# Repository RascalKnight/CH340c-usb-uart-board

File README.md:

# USB-C to UART Converter Board

A 2-layer PCB that bridges USB-C to a TTL UART interface, built from 
scratch in KiCad using the CH340C USB-to-serial chip. Designed as a 
self-directed learning project to understand USB-C connector requirements, 
UART fundamentals, and full-cycle PCB design (schematic, layout, routing, 
and DRC resolution).

## Overview

This board allows a computer to communicate with a microcontroller or 
other UART-based device over USB-C, exposing TX, RX, GND, and VCC on a 
simple header. It replaces the need for a legacy USB-A to serial adapter 
with a compact, modern USB-C native solution.

## Key Design Features

- **CH340C** USB-to-UART bridge IC (crystal-less variant, integrated 
  clock)
- **USB-C receptacle (16P)** with correctly implemented CC1/CC2 pull-down 
  resistors (5.1kΩ) for proper USB-C power negotiation as a UFP (device)
- Standard **VBUS decoupling** (10µF + 0.1µF) and **V3 pin decoupling** 
  per CH340C's 5V power configuration
- Direct D+/D- routing from the USB-C connector to the CH340C's UD+/UD- 
  pins, verified pin-by-pin against the datasheet to avoid a reversed 
  connection
- 4-pin 2.54mm header output (VCC, GND, TXD, RXD) for standard jumper 
  wire compatibility

## Design Challenges Solved

- Diagnosed a **thermal relief spoke count DRC error** on the MCU's 
  fine-pitch GND pads, resolved by switching to a solid zone connection 
  for those specific pads
- Identified and resolved a **hole clearance violation** between the 
  USB-C connector's mechanical mounting holes and adjacent GND pads, 
  distinguishing it from a standard copper clearance issue
- Corrected a **decoupling capacitor placement issue** during layout 
  review, moving caps to sit directly against their associated IC pins
- Fixed an incorrect **RESET pull-up voltage rail** (was tied to 5V on a 
  3.3V-powered MCU) during an earlier related board, applying that lesson 
  here for correct voltage domain separation

## Files

- `.kicad_sch` / `.kicad_pcb` — full KiCad source project
- Schematic PDF export
- 3D board render

## Tools

Designed entirely in KiCad 10.

## Status

Schematic and layout complete, DRC clean. Not yet fabricated/assembled.

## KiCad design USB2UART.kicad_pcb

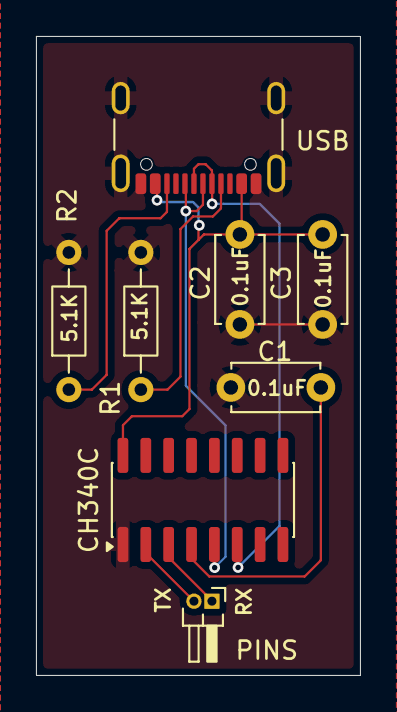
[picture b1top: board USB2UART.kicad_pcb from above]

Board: 2 copper layers, 18.0 x 35.5 mm, 8 parts (0 on the bottom side), 9 nets.

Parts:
C1, C2: 0.1uF; C_Disc_D4.7mm_W2.5mm_P5.00mm
C3: 10uF; C_Disc_D4.7mm_W2.5mm_P5.00mm
CH340C: CH340C; SOIC-16_3.9x9.9mm_P1.27mm
PINS: Conn_01x02_Pin; PinHeader_1x02_P1.00mm_Horizontal
R1, R2: 5.1K; R_Axial_DIN0204_L3.6mm_D1.6mm_P7.62mm_Horizontal
USB: USB_C_Receptacle_USB2.0_16P; USB_C_Receptacle_GCT_USB4105-xx-A_16P_TopMnt_Horizontal

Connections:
GND: C1.1, C2.1, C3.1, CH340C.1 (GND), R1.2, R2.2, USB.A1 (GND), USB.A12 (GND), USB.B1 (GND), USB.B12 (GND), USB.SH (SHIELD)
unnamed: R1.1, USB.A5 (CC1)
unnamed: R2.1, USB.B5 (CC2)
unnamed: CH340C.3 (RXD), PINS.1
unnamed: CH340C.2 (TXD), PINS.2
unnamed: CH340C.5 (UD+), USB.A6 (D+), USB.B6 (D+)
unnamed: CH340C.6 (UD-), USB.A7 (D-), USB.B7 (D-)
unnamed: C1.2, CH340C.4 (V3)
unnamed: C2.2, C3.2, CH340C.16 (VCC), USB.A4 (VBUS), USB.A9 (VBUS), USB.B4 (VBUS), USB.B9 (VBUS)
